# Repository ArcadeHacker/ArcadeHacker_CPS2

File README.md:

# No-Battery-CPS2
Run CPS2 'B' boards with original roms without a battery

Forked from: https://github.com/ArcadeHacker/ArcadeHacker_CPS2

*** TESTED BY ME AND WORKING ON: ***
* 93646B-6 model B board (X-Men: Children of the Atom, xmcotau)
* 93646B-6 model B board (Marvel Super Heroes, mshu)
* 93646B-3 model B board (Alien vs Predator, avspu)

*** Current Issues reported by Artemio: ***
* ~~Not working on~~ B board revision 93646B-4 needs a 75 ohm resistor in series from the CLOCK signal (CN2 A31) to the Arduino (D11). He also stated he had to connect 5V from the B board to Vin on the Arduino rather than Arduino's 5V pin (this seems like this would cause too much voltage drop on the Arduino according to the specs, but maybe it's more tolerable than expected).
* B board revision 97691A-3 is very picky about 5v power (lower/higher slight voltage changes such as 4.85v/5.15v might make the Arduino unstable)

The purpose of this is to install a Arduino in each CPS B board so that it will write the decryption key every time you boot the game. This will allow you to keep the original unaltered roms, but be able to remove the battery and not have to worry about it leaking and causing damage to the PCB.

This is intended to be used on a Arduino Nano due to the small form factor, but should work on other Arduino versions as well. You will need to be connected (soldered) to the CPS2 B board as specified in the original ArcadeHacker_CPS2 programming guide, but without the need of a LCD Shield:

+5V     - Arudino 5V

DATA    - Arduino # 2

SETUP1  - Arduino # 3

CLOCK   - Arduino # 11

SETUP2  - Arduino # 12

GND     - Arduino GND

NOTE: You will need to edit the .ino file to change the value of "const unsigned char Key[] PROGMEM = ..." to the decryption key of the game you will be installing this in.

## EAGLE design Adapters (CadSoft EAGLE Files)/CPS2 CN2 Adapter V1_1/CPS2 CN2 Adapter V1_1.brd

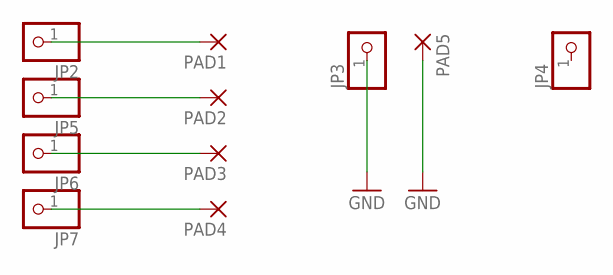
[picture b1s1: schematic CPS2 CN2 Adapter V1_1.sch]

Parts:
JP2, JP3, JP4, JP5, JP6, JP7: PINHD-1X1; 1X01
PAD1, PAD2, PAD3, PAD4, PAD5: SMD2; SMD1,27-2,54

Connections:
GND: JP3.1, PAD5.1
unnamed: JP2.1, PAD1.1
unnamed: JP5.1, PAD2.1
unnamed: JP6.1, PAD3.1
unnamed: JP7.1, PAD4.1

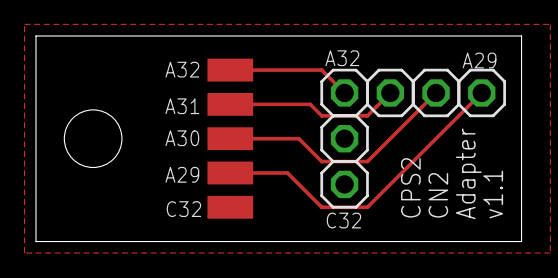
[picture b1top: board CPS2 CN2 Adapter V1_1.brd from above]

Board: 2 copper layers, 27.0 x 11.4 mm, 11 parts (0 on the bottom side), 5 nets.

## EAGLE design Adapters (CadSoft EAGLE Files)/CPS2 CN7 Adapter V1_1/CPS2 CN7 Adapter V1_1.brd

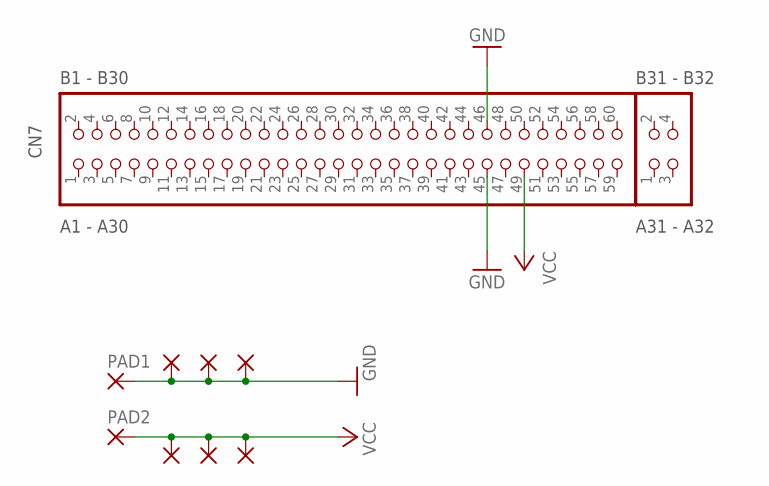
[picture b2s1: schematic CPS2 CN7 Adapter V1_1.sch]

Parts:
JP1: PINHD-2X30; 2X30
JP2: PINHD-2X2; 2X02
PAD1, PAD2, PAD3, PAD4, PAD5, PAD6, PAD7, PAD8: SMD2; SMD1,27-2,54

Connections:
GND: JP1.45, JP1.46, PAD1.1, PAD3.1, PAD5.1, PAD6.1
VCC: JP1.49, PAD2.1, PAD4.1, PAD7.1, PAD8.1

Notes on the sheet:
CN7
A1 - A30
B1 - B30
B31 - B32
A31 - A32

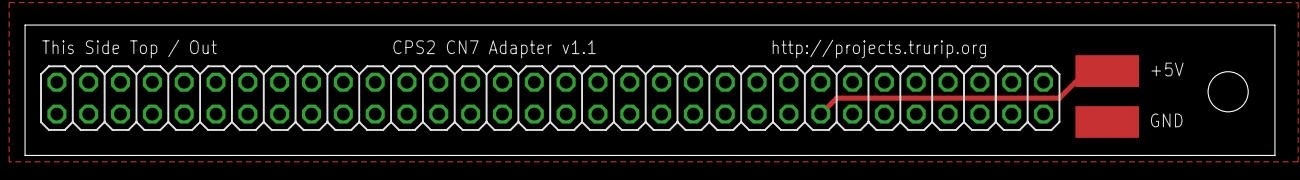
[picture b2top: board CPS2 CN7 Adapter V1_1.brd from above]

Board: 2 copper layers, 99.7 x 10.4 mm, 10 parts (0 on the bottom side), 2 nets.

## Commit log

2016-09-13 Initial release
2016-09-19 Fixes and new games
    Fixed keys for batcirj, spf2t. Added games: ringdesth, spf2tu, ssf2th.
    Thank you smf.
2016-10-18 Updated guide
    General corrections
2016-10-20 CN2 & CN7 Adapters (CadSoft EAGLE Files)
    CN2 / CN7 used for board revisions 93646B-3 and 93646B-4
    CN7 used for board revisions 93646B-5
2018-01-06 Update 1.06
    Added back clones to avoid user confusion. Added ssf2tba, xmcotab. Modified clock signal order for improved compatibility with board revs 4 & 5.
2018-01-06 Revert "Merge branch 'master' of https://github.com/ArcadeHacker/ArcadeHacker_CPS2"
    This reverts commit a1d171e0b6121639965f4d1d0d37b8576c67b080, reversing
    changes made to b0a24301ca7c77082669d4d65f21f78a544988d0.
2018-10-09 Initial commit after fork
    Currently untested on actual hardware.
2018-10-11 Boot time drastically reduced
2018-10-13 More boards tested
2018-10-16 moved pins to high-impedance state after programing
    Original code was never intended to run along the game.
    This might be a non issue, but could create bus conflicts that could stress the Arduino or board in the long run specially on revision 3 and 4 boards.
    Also added a blink to the led after flashing the keys, as a visual cue just after the blink for boot.
2018-10-19 Noted issues reported
2018-10-19 Comment update regarding 5V/VIN
2018-10-20 revision 93646B-4 fix
2018-12-09 Version 1.07
    Fixed keys for batcirj, spf2t, previously broken again in 1.06. Thanks Konosuke.
2021-08-09 refactor: move common game data and routines to separate headers
    game-data.h and cps2.h will be shared with the Arduino Duemilanove port.
2021-08-09 CPS-2 Desuicider for Arduino Duemilanove
2021-10-10 deumilanove: add a quick-tap mode for jumping forward by 10
2021-10-10 deumilanove: print all games on startup
2022-06-27 Update Capcom CPS2 Security Programming Guide.pdf
    Updated programming guide, removed broken download link
